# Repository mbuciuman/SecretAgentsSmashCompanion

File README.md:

# Secret Agent's Smash Companion
This project implements an in-line Gamecube Controller adapter which can modify GC controller inputs, primarily for practicing against a virtual opponent in Smash Bros. Ultimate (or Melee). The adapter exists in-line with your controller, so you do not need to modify the controller nor the console to use it. The adapter primarily uses an Arduino Nano in conjuction with a logic-level converter to step-down the Arduino Nano's digital logic to the Gamecube's 3.3 V data line.

## Getting Started
Below are instructions on how to build and upload the code to an Arduino Nano, and how to use the included EAGLE files to get a PCB.

### How to Build and Upload
#### Installing Visual Studio Code
Visual Studio Code was my choice for C++ development. You might have your own preference for IDEs, but this had some nice supportability in inherent functionality and extensions that I found useful. 

You can get Visual Studio Code for free here:
https://code.visualstudio.com/

#### Setting up PlatformIO
I personally found PlatformIO in conjunction with Visual Studio Code to be better than the Arduino IDE for development. Assuming this is expanded to support multiple microcontrollers (ideally with more SRAM), this would make it easy for deployment and testing across a set of enviroments.

PlatformIO can be installed as an extension in Visual Studio Code: https://marketplace.visualstudio.com/items?itemName=platformio.platformio-ide

#### Setting up Nicohood/Nintendo Library
The Nintendo library contains all the APIs for interfacing with the controller and console. You can install it by navigating to the "Libraries" in PlatformIO, searching for the "Nintendo" library, and then selecting "Install".

#### Building and Uploading to the Arduino Nano

Connect your Arduino Nano and click on the PlatformIO icon on Visual Studio Code's Activity bar. Select "Upload" from the "Project Tasks", and PlatformIO will begin to build and upload the code to the connected Arduino.

__NOTE:__ You may have to change the `upload_port` variable in `platformio.ini` to match the Arduino's upload port.

Assuming it builds successfully, your code should be on the Arduino and immediately start running.

### How to Assemble
I included my own designs of a PCB which should make it simple to put together all the necessary parts.

#### Manufacture PCB
I personally like to use OSH Park's 2-layer prototype offering where they will send you 3 PCBs printed from your schematic for a pretty affordable price. For me it was ~12 bucks with shipping, after which it was printed and arrived after 2 weeks.

Link to website: https://oshpark.com/

#### Board Components
Here are the things you should need:
* Official Arduino Nano: https://www.amazon.com/Arduino-A000005-ARDUINO-Nano/dp/B0097AU5OU/
OR
* Arduino Nano Clone: https://www.amazon.com/ELEGOO-Arduino-ATmega328P-Without-Compatible/dp/B0713XK923/ref=sr_1_4?keywords=arduino+nano&qid=1551589218&s=gateway&sr=8-4

__NOTE:__ If you get the Arduino Nano Clone, you may need to change the `board` var in `platformio.ini` depending on its bootloader.

* Bi-directional Logic Level Converter: https://www.sparkfun.com/products/12009
* Gamecube Controller Extension Cable: https://www.amazon.com/gp/product/B001AI7CF2/ref=oh_aui_search_asin_title?ie=UTF8&psc=1
* Header pins (__NOTE:__ should only be needed if the Arduino or the BLLC do not come with header pins already): https://www.sparkfun.com/products/116
* Project box (optional): https://www.amazon.com/gp/product/B00CSRW6UU/ref=ppx_yo_dt_b_asin_title_o00_s00?ie=UTF8&psc=1

#### Assemble Components
Once you have all the parts, you should be able to solder the Arduino Nano and the Bi-directional Logic Level Converter to their header pins, and then directly to the PCB.

For the GC_CONS and GC_CONT pins, you'll have to determine which wires inside of the extension cable corresponds to the pins. There should be 5 wires inside the cable: 5V (for the rumble servo), 3.3V, the Data signal, and two Ground.

There are two methods to determine which ones correspond to which, and both require stripping each individual wire and using a multimeter.

The first method would be to plug in the male-end of the extension cable into a Gamecube (or adapter) and turning it on. Set your multimeter to detect voltage and match each colored wire to its function through the corresponding voltage. The data line should be somewhere between 3.3V and 0V.

The second method would be to set your multimeter to test continuity, then match up each wire to each termination on the female-end of the socket. The document (also linked with other goodies in the Nicohood/Nintendo repo) has an in-depth guide on how to match up the wires with their associated inputs:

http://www.int03.co.uk/crema/hardware/gamecube/_gc-control1.html

For reference, my wires and their corresponding inputs (on the extension cable I linked in the parts list above) given the image in the document above are listed below:
```
Pin 1: White - 5 V
Pin 2: Red - DATA (3.3V)
Pin 3: Yellow - GND
Pin 4: Black - GND
Pin 5: NOT CONN - NOT CONN
Pin 6: Green - 3.3V
Pin 7: NOT CONN - NOT CONN
```
After determining which wires represent which inputs, you should be able to strip the wires and solder them to the board's pins.

I *HIGHLY* recommend using hot glue on the GC_CONS and GC_CONT inputs as the wires are flimsy and can be easily pulled out of the board.

Also, putting the board into a project box will give it further protection. The one I linked above is a transparent, polycarbonate one that I personally used. On top of this, if you choose not to use hot glue, you can use cable glands instead to keep the cables in place on the PCB.

#### Connecting to Console
The adapter should work immediately after plugging it into the console, and you should be able to see the controller being detected by the Gamecube/Switch as if it was just another controller. The Arduino Nano's light should be on showing that it's powered.

If you notice that inputs are not going through and the Arduino light is on, press and hold L+R+A+B to reset the controller, and if that doesn't work, try holding X+Y+START as well.

If it still doesn't work, I would recommend uncommenting the `#define DEBUG` directive in `Constants.hpp`, and commenting out the `#define WRITE` directive to triage the controller input reading.

## Usage

Once you've connected the adapter to the console and the controller is sending all inputs to the console successfully, you'll be able to use the training modes listed below.

### General
Each training mode is mapped in some way to the D-Pad inputs. With the adapter plugged in, no D-Pad inputs will be sent to the console, but will instead be how you select between different training modes. The rest of the controller inputs will be sent unmodified to the console until a training mode is selected.

Each D-Pad direction has a number of different training modes associated with it. So, in order to select a specific mode, you have to press the associated D-Pad direction a certain number of times to cycle to the desired mode.

There are two ways to exit the current mode and return to sending all user-inputs through to the console.
The first is to continue to press the D-Pad direction in the same direction as the current mode until you reach the last mode, then press the D-Pad in the direction one last time (e.g. When in the Mash Jump mode, tap D-Pad Left twice).
The second is to press the D-Pad direction in a different direction than the current mode (e.g. tap D-Pad Down when in the Random DI training mode).

The modes bound to each D-Pad input are listed below:

### DI Training (D-Pad Left)

There are two training modes on D-Pad Left:

* Left/Right DI: inputs left and right DI with a neutral analog stick input alternating between them
* Random DI: inputs DI in a random direction with a neutral analog stick input alternating between each random DI input

### Escape Option Training (D-Pad Right)

There are two training modes on D-Pad Right:

* Mash Jump: inputs jumps continuously
* Mash Air-dodge: inputs air-dodge inputs in random directions

### Input Recording and Input Playback (D-Pad Down and D-Pad Up)

In order to record user input, you can press D-Pad Down to start recording, then press any other D-Pad direction to stop, similar to exiting other modes. You can re-record by pressing D-Pad Down again and following the same steps, but only one recording can be stored at a time, so it will overwrite your previously-recorded inputs. Once you're satisfied with your recording, press D-Pad Up to enter the playback recording mode. It will begin to playback your recording and overwrite any inputs into the console. In a similar fashion for exiting other modes, you can press any D-Pad direction to stop playback.

#### Input Recording Architecture

The most complicated part of this project was implementing input recording and playback. I decided to make this a separate section as there will likely be a number of questions involving this piece of functionality.

For storing recordings of input, I decided that the most optimal method would be to store the controller state only when the controller's state changes, rather than the full state of the controller every processor cycle. `InputChangeStore` represents the full recording of the input and is intialized using the initial controller state at the start of the recording along with the time of the initial state. Each processor cycle, the state of the controller is compared with the initial/previous controller state of the recording. Each time the controller state changes, the new state is then stored as an entry into the array of `InputChange` objects within `InputChangeStore`. Each `InputChange` object stores the full state of the controller along with the total time that controller state should exist. *NOTE*: If the storage capacity for recording is exhausted, this will cause recording mode to be silently exited back into the default pass-through mode. However, whatever was recorded can still be played back.

Playback is achieved by pushing the stored state of the controller to the console every processor cycle. Once the state's time has finished elapsing, the current state index is incremented, and the next controller state is then pushed to the console. Once the recording is finished being played back, it starts over and continues to loop until the playback mode is exited.

##### Tweaking and Caveats

One of the biggest challenges on top of getting the above functionality to work was optimizing the logic in the previous section so that the Arduino Nano can store in its SRAM a reasonable amount of controller data for training against specific inputs or combos. As all of the variables in this project are statically-allocated, I had to pre-define some constants in `Constants.hpp` to be able to finely tweak the memory usage of the program. The following should be noted for anyone who's looking to further tweak or change input recording.

`ALLOWABLE_AXIS_DRIFT`: This constant defines the minimum value by which any of the 6 axes must change in order to be stored as a new controller state. I noticed that setting this to `0` resulted in the SRAM on the Arduino quickly being used up as my controller seemed to have its axes drift by about `2` or so every frame. Setting this to `2` resulted in tilts or smash attacks also somewhat quickly exhausting the SRAM. If I set this too high, I noticed some specific inputs occasionally becoming smash attacks, so through testing, I opted for `5` having a good balance between accuracy and memory usage. If you're seeing some differences between recording and playback, you can try to reduce this to a lower number.

`MAX_STORE_SIZE`: The total number of `InputChange` objects to store. This is currently set to `180` as it's around the maximum number of objects that can be stored on the Arduino Nano. If you end up adding more constants, classes, etc. to the codebase, this will reduce the total SRAM that the Arduino Nano will have available, and so this variable will have to be reduced. When building the project, PlatformIO should give you a report of how much SRAM is being used by the project. I did noticed through some testing that there seems to be some dynamic allocation done either by the Nintendo library, or something else, so ensuring that there are around 100 bytes left over of SRAM should guarantee that those dynamic resources are allowed to be put into SRAM without locking the program up.

## Specific Configuration Options

Refer to `Constants.hpp` for specific variables which can be used to debug or modify the behavior of the program. 

## How to Add Your Own Training Mode

Training Modes or new Training Groups can be added by extending their respective parent classes using other Training Modes and Groups as templates.

## Utilized Licensed Software

* Nicohood Nintendo Library (see link below for License):
https://github.com/NicoHood/Nintendo

* Arduino Eagle CAD Library (used modified Arduino Nano schematic + board) [GPLv3]:
https://github.com/cyberlink1/Arduino-Eagle-Cad-Library

## Miscellaneous

### Gamecube Controller USB Adapter Compatibility
I have successfully tested this code against an Arduino Nano plugged into a Nintendo Gamecube and the official Nintendo 4-port Gamecube Adapter. While I also tried to test the board against a Mayflash 4-port [W012] adapter, I had no luck. YMMV however as some people have reported some Arduinos using Nicohood's Nintendo library working with the Mayflash adapters.

### Author's Note
Just a heads up, this is my first official open-source, C++, and serious embedded development project, so feel free to send me suggestions and improvements. I primarily have studied and developed in Java, C#, and Python, so C++ has been interesting to work with to say the least.

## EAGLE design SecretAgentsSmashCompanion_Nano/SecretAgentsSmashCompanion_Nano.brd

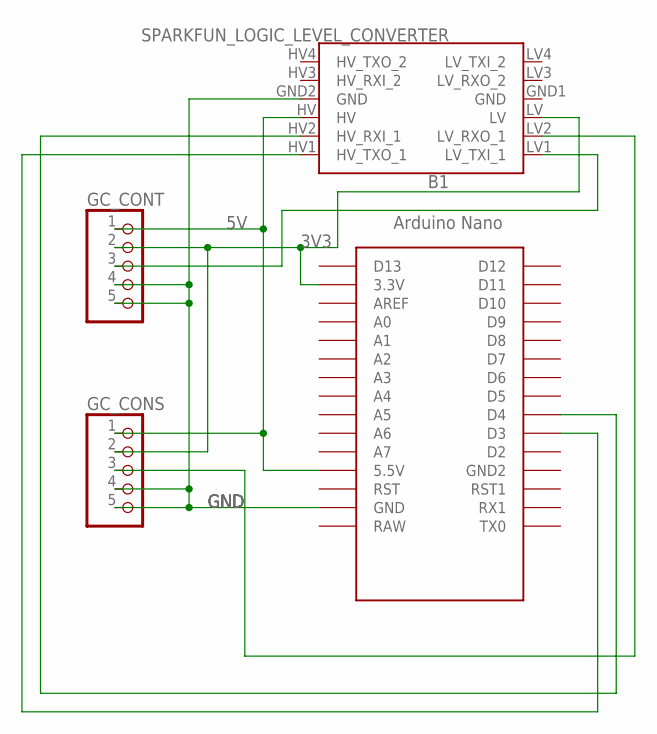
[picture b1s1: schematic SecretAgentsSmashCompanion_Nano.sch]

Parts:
B1: SPARKFUN_LOGIC_LEVEL_CONVERTER
GC_CONS: PINHD-1X5; 1X05
GC_CONT: PINHD-1X5; 1X05
U$2: NANO

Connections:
3V3: B1.LV, GC_CONS.2, GC_CONT.2, U$2.3.3V
5V: B1.HV, GC_CONS.1, GC_CONT.1, U$2.5V (5.5V)
GND: B1.GND1 (GND), B1.GND2 (GND), GC_CONS.4, GC_CONS.5, GC_CONT.4, GC_CONT.5, U$2.GND
unnamed: B1.LV2 (LV_RXO_1), GC_CONS.3
unnamed: B1.LV1 (LV_TXI_1), GC_CONT.3
unnamed: B1.HV2 (HV_RXI_1), U$2.D4
unnamed: B1.HV1 (HV_TXO_1), U$2.D3

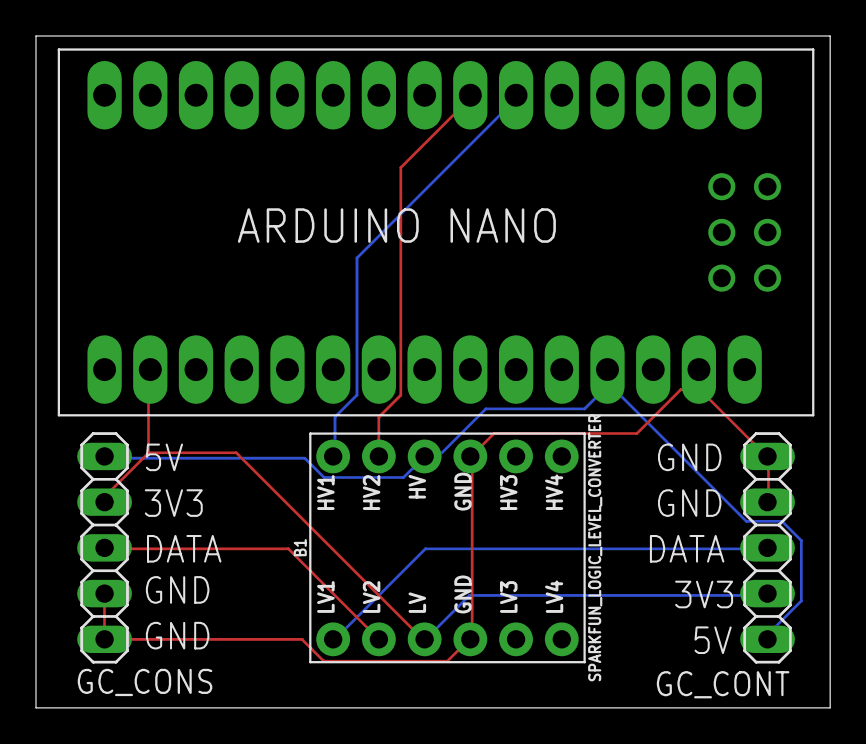
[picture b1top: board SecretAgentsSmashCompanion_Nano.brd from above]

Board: 2 copper layers, 44.1 x 37.3 mm, 4 parts (0 on the bottom side), 7 nets.

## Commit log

2019-02-05 Actual initial commit: Added skeleton DI and EscapeOption files
2019-02-05 Added random DI, mash jump, and no escape option options
2019-02-05 Reformatted code
2019-02-05 Added mash air-dodge, and fixed building
2019-02-05 Create LICENSE
2019-02-06 Added core-avs-ds library, re-added vscode folder, added example code in setup
2019-02-06 Re-added .vscode to .gitignore (since it was huge)
2019-02-06 Added recording base classes and imported linked list library
2019-02-06 Replaced DI/EscapeOption with over-arching InputModifier, changed header file defines
2019-02-14 Changes: * Added input recording/playback classes * Added input change checking logic * Fixed indentation on all files
2019-02-16 Fixed code with C++ best practices/idioms: added destructors, added 'explicit' to inherited constructors, changed class functions to pass-by-reference-to-'const', changed constructors to use member i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
2019-02-16 Changed unnecessary pointers in function defnitions to references
2019-02-21 Added new InputHandler class to handle processing input changes, added maximum directional input to InputModifiers which generate a random direction, moved InputModifiers into subfolder
2019-02-21 Added InputHandler logic flow to loop(), implemented some input diff and recording methods
2019-02-22 Finished recording logic (meaning main features are complete!!!), and renamed InputHandler modifiers to represent the modifiers bound to each direction
2019-02-24 Converted code base to statically allocated variables, fixed a number of bugs, reorganized project
2019-02-25 Added functionality to customize the maximum number of differing inputs stored when inputs change.
2019-02-27 Added configurable number of button changes stored, moved debug and constants into constants.hpp, added DEBUG #ifdef directive around all serial output
2019-02-27 Added WRITE directive to toggle writing to console, fixed recording+playback logic bugs
2019-03-03 BIG COMMIT: *FULLY IMPLEMENTED INPUT RECORDING/PLAYBACK*, removed DPad inputs from going through (to prevent taunts from coming out), added state enums to InputModifiers, added customizable wait time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
2019-03-03 Removed lib and test folders
2019-03-03 Added PCB schematic and board layouts, added DOXYGEN documentation to code
2019-03-03 Removed symbolic link to Nintendo library
2019-03-03 Removed include folder
2019-03-05 Added SDI Training modes
2019-03-05 Refactored/optimized InputDiff into InputChange class, renamed/refactored various methods to make more sense, renamed static InputModifiers to caps
2019-03-05 Small refactoring of constants and static vars
2019-03-05 Fixed InputModifier definitions/declarations
2019-03-06 Refactored code by adding Utility.hpp and adding 'const' to parameters for clarity, Added SetDI and SetSDI classes
2019-03-06 Changed MashAirdodge to not select a specific random direction when air-dodging
2019-03-06 Added more comments and refactored some vars
2019-03-06 Rebuilt artifacts and fixed some formatting
2019-03-06 Updated InputHandler with new SetDI/SetSDI and updated Constants.hpp with new MAX_STORE_SIZE
2019-03-06 Fixed bugs in SetSDI and DI Selection
2019-03-23 Added OOS Training, added support for custom "Training Groups", made various fixes
2019-08-12 Added photo

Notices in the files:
parts and their libraries:
SparkFun-Boards: Licensing: Creative Commons ShareAlike 4.0 International - https://creativecommons.org/licenses/by-sa/4.0
